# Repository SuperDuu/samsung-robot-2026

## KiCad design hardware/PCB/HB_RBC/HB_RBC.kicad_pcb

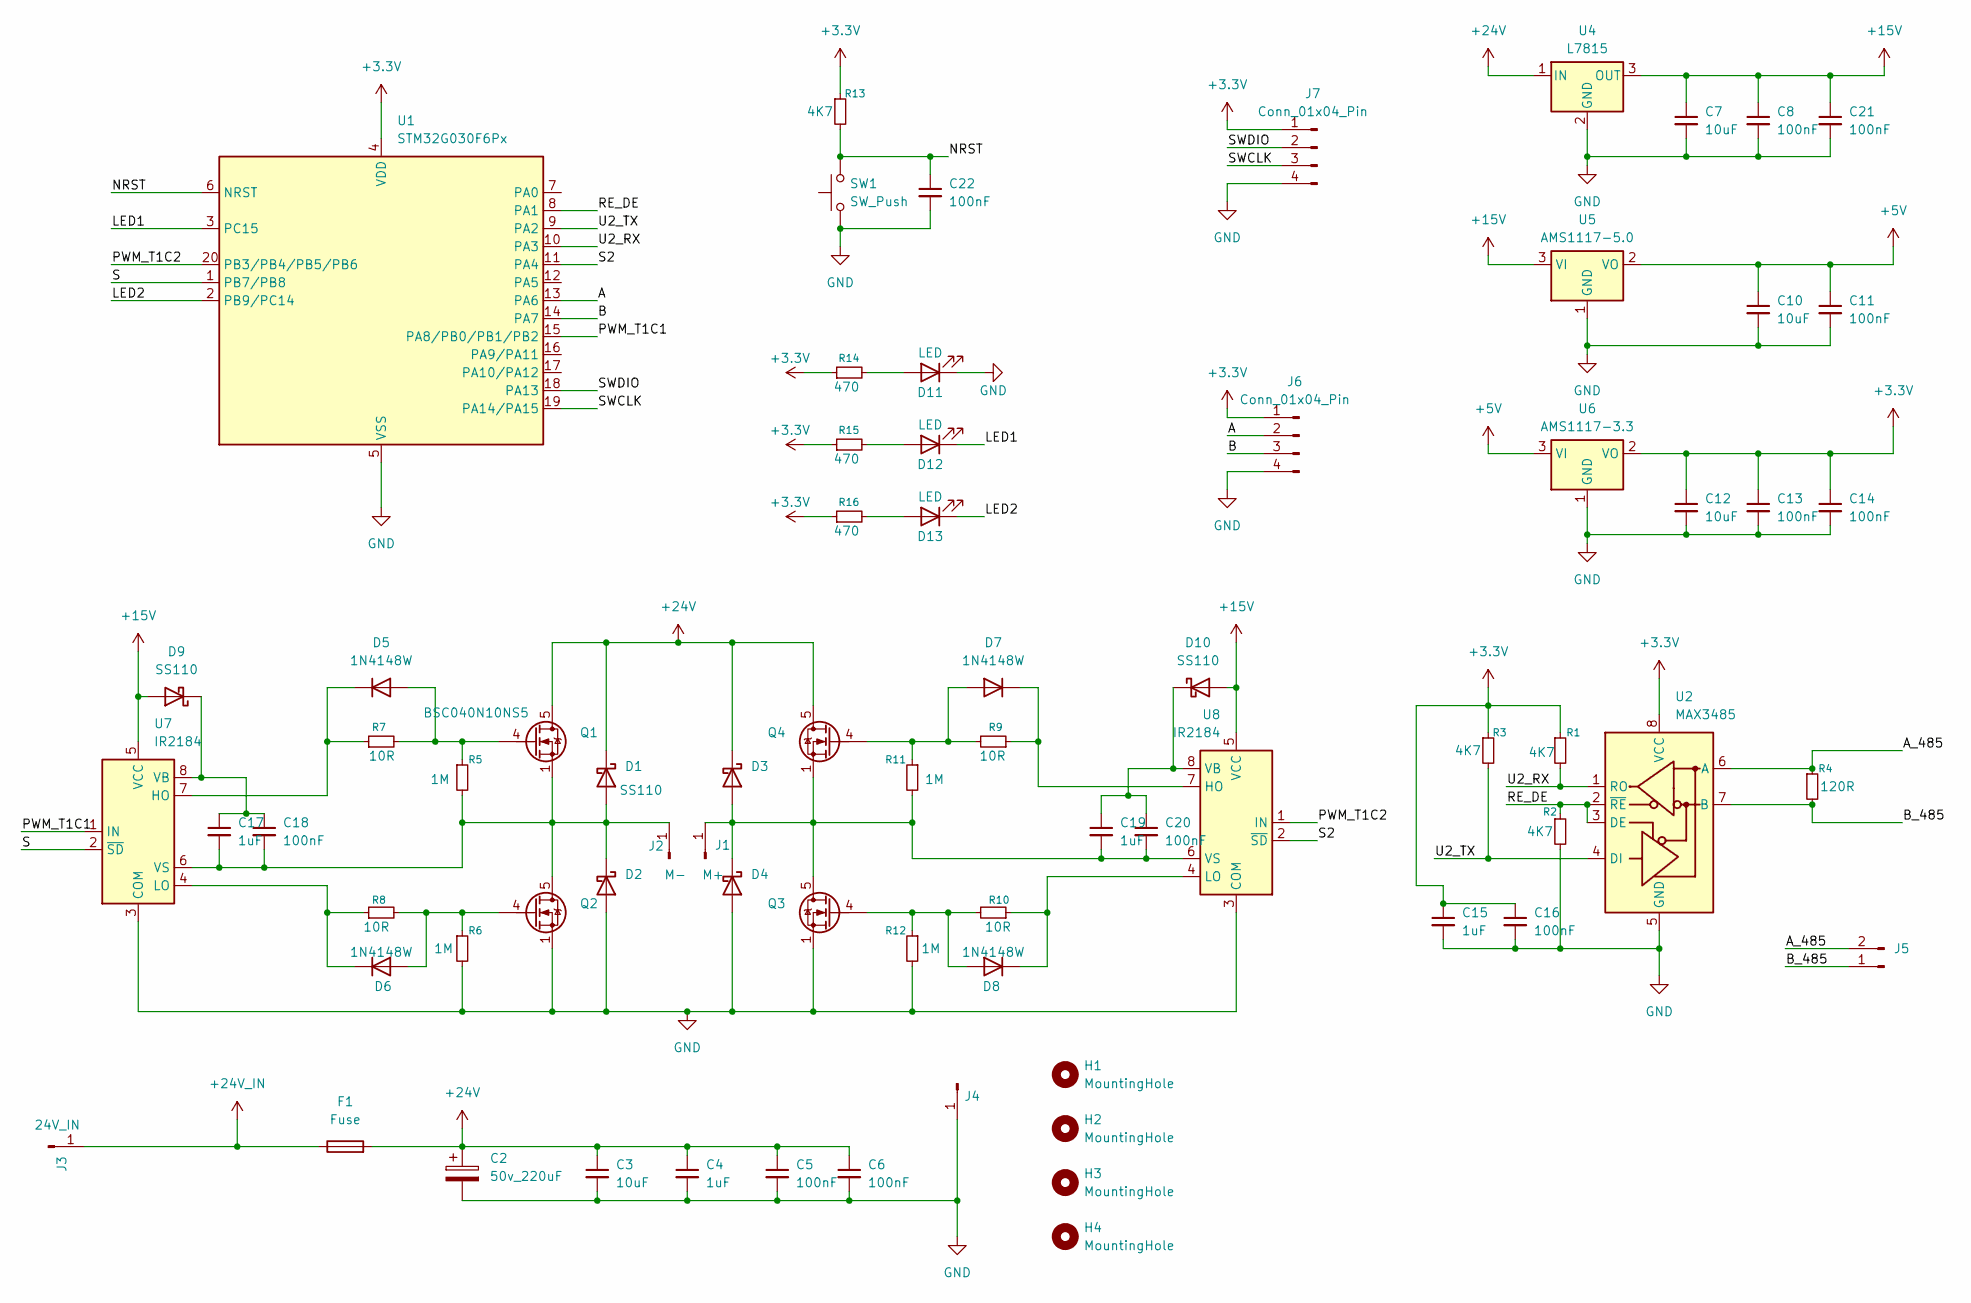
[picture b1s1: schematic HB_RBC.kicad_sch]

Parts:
C2: 50v_220uF; CP_Elec_10x10.5
C3, C7, C10, C12: 10uF; C_0805_2012Metric_Pad1.18x1.45mm_HandSolder
C4, C15, C17, C19: 1uF; C_0805_2012Metric_Pad1.18x1.45mm_HandSolder
C5, C6, C8, C11, C13, C14, C16, C18, C20, C21, C22: 100nF; C_0805_2012Metric_Pad1.18x1.45mm_HandSolder
D1, D9, D10: SS110; D_SMA
D2, D3, D4: D_Schottky; D_SMA
D5, D6, D7, D8: 1N4148W; D_SOD-123
D11, D12, D13: LED; LED_0805_2012Metric_Pad1.15x1.40mm_HandSolder
F1: Fuse; Fuseholder_Cylinder-5x20mm_Schurter_0031_8201_Horizontal_Op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
H1, H2, H3, H4: MountingHole; MountingHole_3.2mm_M3_ISO14580_Pad_TopBottom
J1: M+; SolderWirePad_1x01_SMD_4x8mm
J2: M-; SolderWirePad_1x01_SMD_4x8mm
J3: 24V_IN; SolderWirePad_1x01_SMD_4x8mm
J4: Conn_01x01_Pin; SolderWirePad_1x01_SMD_4x8mm
J5: Conn_01x02_Pin; JST_XH_S2B-XH-A-1_1x02_P2.50mm_Horizontal
J6, J7: Conn_01x04_Pin; JST_XH_S4B-XH-A-1_1x04_P2.50mm_Horizontal
Q1, Q2, Q3, Q4: BSC040N10NS5; TDSON-8-1
R1, R2, R3, R13: 4K7; R_0805_2012Metric_Pad1.20x1.40mm_HandSolder
R4: 120R; R_0805_2012Metric_Pad1.20x1.40mm_HandSolder
R5, R6, R11, R12: 1M; R_0805_2012Metric_Pad1.20x1.40mm_HandSolder
R7, R8, R9, R10: 10R; R_0805_2012Metric_Pad1.20x1.40mm_HandSolder
R14, R15, R16: 470; R_0805_2012Metric_Pad1.20x1.40mm_HandSolder
SW1: SW_Push; SW_Tactile_SPST_NO_Straight_CK_PTS636Sx25SMTRLFS
U1: STM32G030F6Px; TSSOP-20_4.4x6.5mm_P0.65mm
U2: MAX3485; SOIC-8_3.9x4.9mm_P1.27mm
U4: L7815; TO-263-3_TabPin2
U5: AMS1117-5.0; SOT-223-3_TabPin2
U6: AMS1117-3.3; SOT-223-3_TabPin2
U7, U8: IR2184; SOIC-8_3.9x4.9mm_P1.27mm

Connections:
+3.3V: C12.1, C13.1, C14.1, C15.1, C16.1, J6.1, J7.1, R1.1, R3.1, R13.1, R14.1, R15.1, R16.1, U1.4 (VDD), U2.8 (VCC), U6.2 (VO)
+5V: C10.1, C11.1, U5.2 (VO), U6.3 (VI)
+15V: C7.1, C8.1, C21.1, D9.2 (A), D10.2 (A), U4.3 (OUT), U5.3 (VI), U7.5 (VCC), U8.5 (VCC)
+24V: C2.1, C3.1, C4.1, C5.1, C6.1, D1.1 (K), D3.1 (K), F1.2, Q1.5 (D), Q4.5 (D), U4.1 (IN)
+24V_IN: F1.1, J3.1 (Pin_1_1)
/A: J6.2, U1.13 (PA6)
/A_485: J5.2, R4.1, U2.6 (A)
/B: J6.3, U1.14 (PA7)
/B_485: J5.1, R4.2, U2.7 (B)
/LED1: D12.1 (K), U1.3 (PC15)
/LED2: D13.1 (K), U1.2 (PB9/PC14)
/NRST: C22.1, R13.2, SW1.2, U1.6 (NRST)
/PWM_T1C1: U1.15 (PA8/PB0/PB1/PB2), U7.1 (IN)
/PWM_T1C2: U1.20 (PB3/PB4/PB5/PB6), U8.1 (IN)
/RE_DE: R2.1, U1.8 (PA1), U2.2 (~RE), U2.3 (DE)
/S: U1.1 (PB7/PB8), U7.2 (~SD)
/S2: U1.11 (PA4), U8.2 (~SD)
/SWCLK: J7.3, U1.19 (PA14/PA15)
/SWDIO: J7.2, U1.18 (PA13)
/U2_RX: R1.2, U1.10 (PA3), U2.1 (RO)
/U2_TX: R3.2, U1.9 (PA2), U2.4 (DI)
GND: C2.2, C3.2, C4.2, C5.2, C6.2, C7.2, C8.2, C10.2, C11.2, C12.2, C13.2, C14.2, C15.2, C16.2, C21.2, C22.2, D2.2 (A), D4.2 (A), D11.1 (K), J4.1 (Pin_1_1), J6.4, J7.4, Q2.1 (S), Q2.2 (S), Q2.3 (S), Q3.1 (S), Q3.2 (S), Q3.3 (S), R2.2, R6.2, R12.2, SW1.1, U1.5 (VSS), U2.5 (GND), U4.2 (GND), U5.1 (GND), U6.1 (GND), U7.3 (COM), U8.3 (COM)
unnamed: C17.2, C18.2, D1.2 (A), D2.1 (K), J2.1 (Pin_1_1), Q1.1 (S), Q1.2 (S), Q1.3 (S), Q2.5 (D), R5.2, U7.6 (VS)
unnamed: C19.2, C20.2, D3.2 (A), D4.1 (K), J1.1 (Pin_1_1), Q3.5 (D), Q4.1 (S), Q4.2 (S), Q4.3 (S), R11.2, U8.6 (VS)
unnamed: D5.2 (A), Q1.4 (G), R5.1, R7.2
unnamed: D5.1 (K), R7.1, U7.7 (HO)
unnamed: D6.2 (A), Q2.4 (G), R6.1, R8.2
unnamed: D6.1 (K), R8.1, U7.4 (LO)
unnamed: D7.2 (A), Q4.4 (G), R9.2, R11.1
unnamed: D7.1 (K), R9.1, U8.7 (HO)
unnamed: D8.2 (A), Q3.4 (G), R10.2, R12.1
unnamed: D8.1 (K), R10.1, U8.4 (LO)
unnamed: C17.1, C18.1, D9.1 (K), U7.8 (VB)
unnamed: C19.1, C20.1, D10.1 (K), U8.8 (VB)
unnamed: D11.2 (A), R14.2
unnamed: D12.2 (A), R15.2
unnamed: D13.2 (A), R16.2

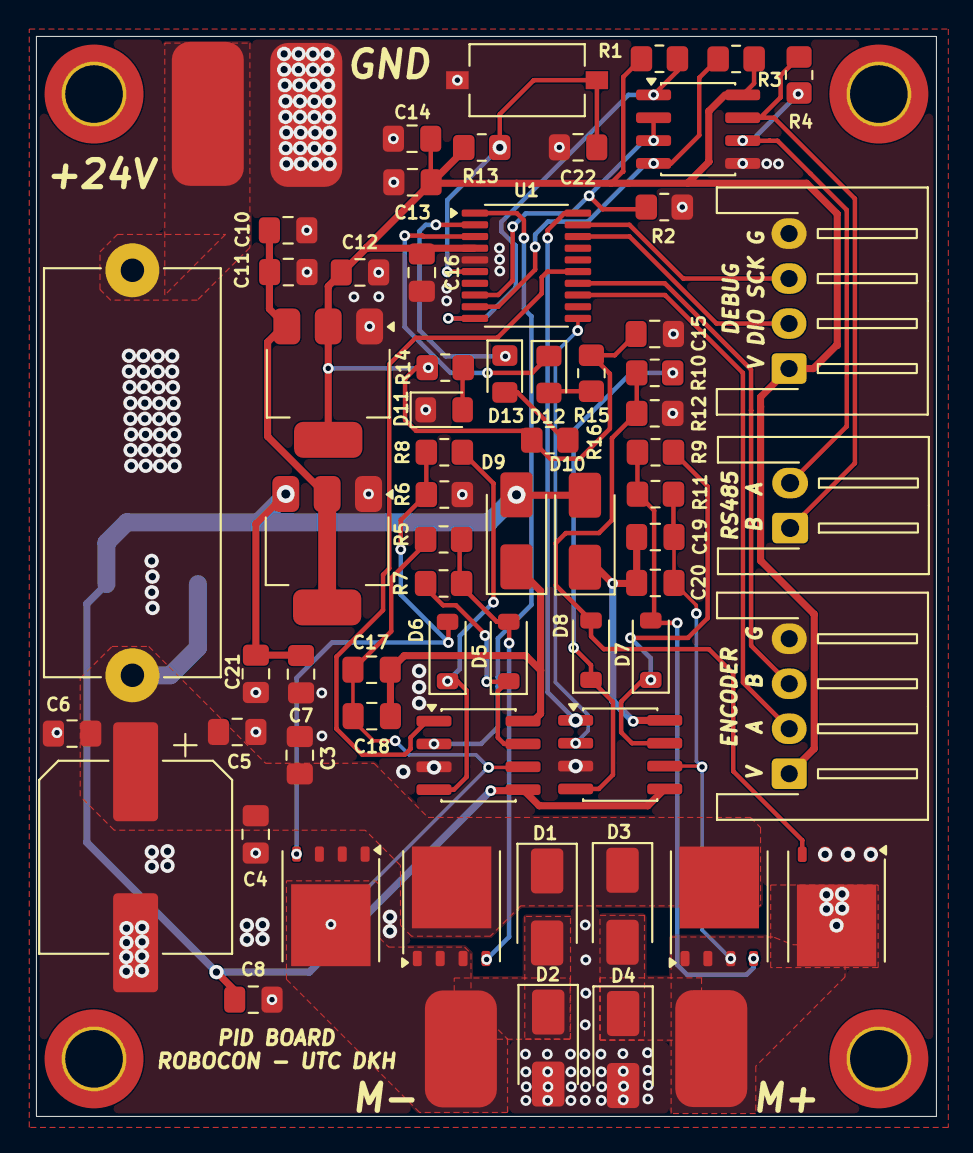
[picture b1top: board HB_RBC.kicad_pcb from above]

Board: 2 copper layers, 50.0 x 60.0 mm, 73 parts (1 on the bottom side), 37 nets.

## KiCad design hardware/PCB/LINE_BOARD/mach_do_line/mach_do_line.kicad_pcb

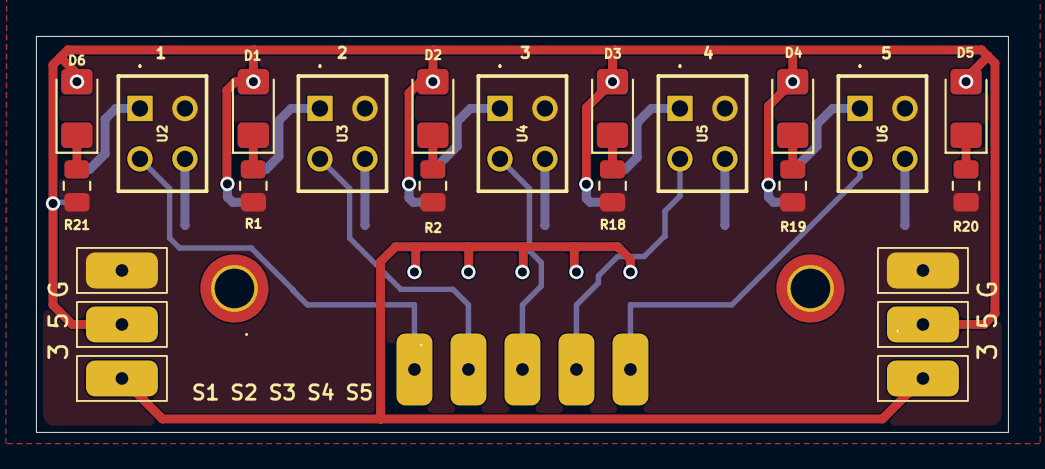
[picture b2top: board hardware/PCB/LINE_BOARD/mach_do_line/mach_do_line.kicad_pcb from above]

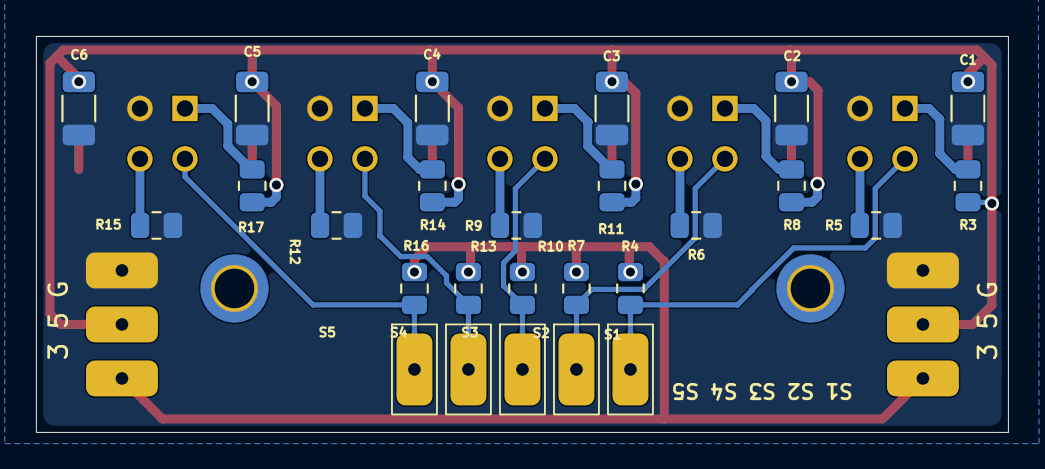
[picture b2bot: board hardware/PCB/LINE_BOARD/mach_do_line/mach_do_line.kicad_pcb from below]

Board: 2 copper layers, 54.0 x 22.0 mm, 51 parts (26 on the bottom side), 24 nets.

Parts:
C1, C2, C3, C4, C5, C6: 100uF; C_1206_3216Metric
D1, D2, D3, D4, D5, D6: LED_Small; LED_1206_3216Metric_Pad1.42x1.75mm_HandSolder
H1, H2: MountingHole; MountingHole_2.2mm_M2_ISO14580_Pad_TopBottom
J2, J3, J10, J11, J12, J13, J14, J15, J16, J17, J18: Conn_01x01_Pin; PAD-2x4mm-SMD
R1, R2, R18, R19, R20, R21: 220; R_0805_2012Metric
R3, R8, R11, R14, R17: 220R; R_0805_2012Metric
R4, R7, R10, R13, R16: 10K; R_0805_2012Metric
R5, R6, R9, R12, R15: 100R; R_0805_2012Metric
U2, U3, U4, U5, U6: RPR-220; RPR220

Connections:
+3V3: J3.1 (Pin_1_1), J15.1 (Pin_1_1), R4.2, R7.2, R10.2, R13.2, R16.2
+5V: C1.1, C2.1, C3.1, C4.1, C5.1, C6.1, D1.2 (A), D2.2 (A), D3.2 (A), D4.2 (A), D5.2 (A), D6.2 (A), J13.1 (Pin_1_1), J16.1 (Pin_1_1), R3.1, R8.1, R11.1, R14.1, R17.1
/s1: J2.1 (Pin_1_1), R4.1, U2.4 (C)
/s2: J10.1 (Pin_1_1), R7.1, U3.4 (C)
/s3: J11.1 (Pin_1_1), R10.1, U4.4 (C)
/s4: J12.1 (Pin_1_1), R13.1, U5.4 (C)
/s5: J18.1 (Pin_1_1), R16.1, U6.4 (C)
GND: C1.2, C2.2, C3.2, C4.2, C5.2, C6.2, J14.1 (Pin_1_1), J17.1 (Pin_1_1), R1.2, R2.2, R5.2, R6.2, R9.2, R12.2, R15.2, R18.2, R19.2, R20.2, R21.2, U2.2 (K), U3.2 (K), U4.2 (K), U5.2 (K), U6.2 (K)
unnamed: D1.1 (K), R1.1
unnamed: D2.1 (K), R2.1
unnamed: D3.1 (K), R18.1
unnamed: D4.1 (K), R19.1
unnamed: D5.1 (K), R20.1
unnamed: D6.1 (K), R21.1
unnamed: R3.2, U2.1 (A)
unnamed: R5.1, U2.3 (E)
unnamed: R8.2, U3.1 (A)
unnamed: R6.1, U3.3 (E)
unnamed: R11.2, U4.1 (A)
unnamed: R9.1, U4.3 (E)
unnamed: R14.2, U5.1 (A)
unnamed: R12.1, U5.3 (E)
unnamed: R17.2, U6.1 (A)
unnamed: R15.1, U6.3 (E)

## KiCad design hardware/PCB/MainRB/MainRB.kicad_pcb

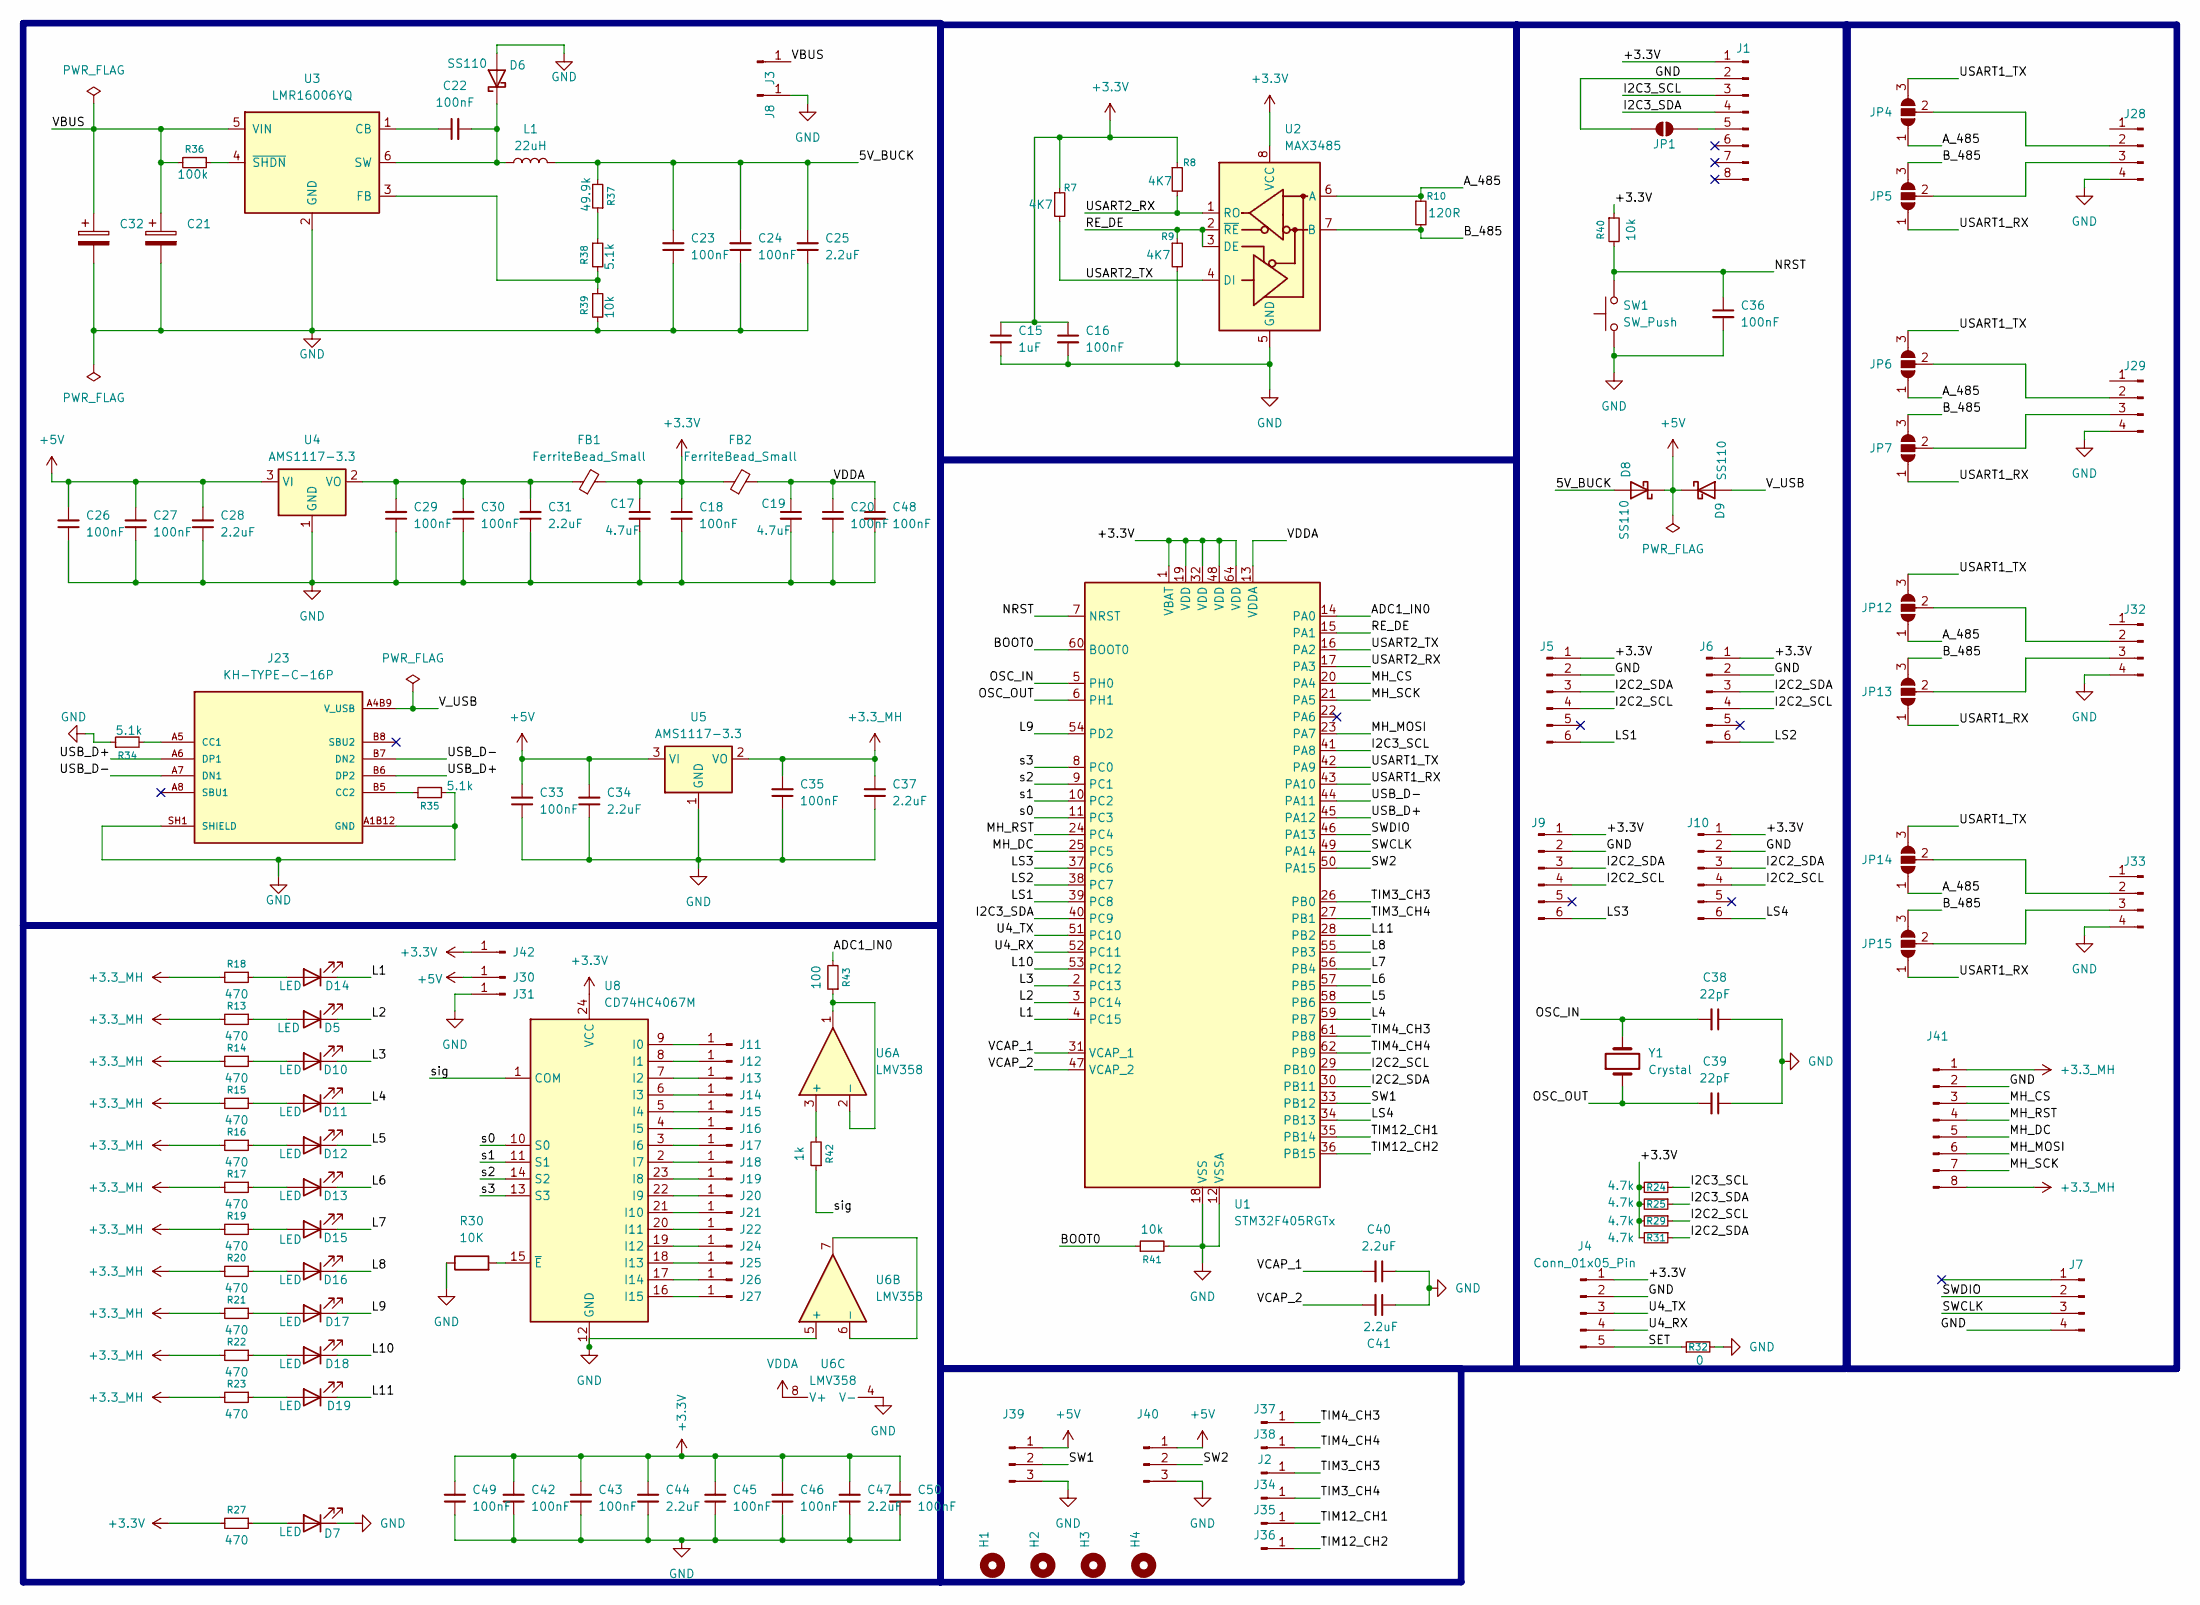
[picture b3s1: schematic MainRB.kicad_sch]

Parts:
C15: 1uF; C_0805_2012Metric_Pad1.18x1.45mm_HandSolder
C16, C18, C20, C22, C23, C24, C26, C27, C29, C30, C33, C35, C36, C42, C43, C45, C46, C48, C49, C50: 100nF; C_0805_2012Metric_Pad1.18x1.45mm_HandSolder
C17, C19: 4.7uF; C_0805_2012Metric_Pad1.18x1.45mm_HandSolder
C21, C32: C_Polarized; CP_Elec_10x10.5
C25, C28, C31, C34, C37, C40, C41, C44, C47: 2.2uF; C_0805_2012Metric_Pad1.18x1.45mm_HandSolder
C38, C39: 22pF; C_0805_2012Metric_Pad1.18x1.45mm_HandSolder
D5, D7, D10, D11, D12, D13, D14, D15, D16, D17, D18, D19: LED; LED_0805_2012Metric
D6, D8, D9: SS110; D_SMA
FB1, FB2: FerriteBead_Small; L_0603_1608Metric_Pad1.05x0.95mm_HandSolder
H1, H2, H3, H4: MountingHole; MountingHole_3.2mm_M3_ISO14580_Pad_TopBottom
J1: Conn_01x08_Pin; PinHeader_1x08_P2.54mm_Vertical
J2, J34, J35, J36, J37, J38: Conn_01x01_Pin; SolderWirePad_1x01_SMD_2x4mm
J3, J8: 24V_IN; SolderWirePad_1x01_SMD_4x8mm
J4: Conn_01x05_Pin; PinHeader_1x05_P2.54mm_Vertical
J5, J6, J9, J10: Conn_01x06_Pin; JST_XH_S6B-XH-A_1x06_P2.50mm_Horizontal
J7: Conn_01x04_Pin; JST_XH_B4B-XH-A_1x04_P2.50mm_Vertical
J11, J12, J13, J14, J15, J16, J17, J18, J19, J20, J21, J22, J24, J25, J26, J27, J30, J31, J42: Conn_01x01_Pin; SolderWirePad_1x01_SMD_1x2mm
J23: KH-TYPE-C-16P; KINGHELM_KH-TYPE-C-16P; PARTREV A0
J28, J29, J32, J33: Conn_01x04_Pin; JST_XH_S4B-XH-A-1_1x04_P2.50mm_Horizontal
J39, J40: Conn_01x03_Pin; JST_XH_B3B-XH-A_1x03_P2.50mm_Vertical
J41: Conn_01x08_Pin; JST_XH_B8B-XH-A_1x08_P2.50mm_Vertical
JP1: SolderJumper_2_Open; SolderJumper-2_P1.3mm_Open_Pad1.0x1.5mm
JP4, JP5, JP6, JP7, JP12, JP13, JP14, JP15: SolderJumper_3_Open; SolderJumper-3_P1.3mm_Open_RoundedPad1.0x1.5mm_NumberLabels
L1: 22uH; L_TracoPower_TCK-047_5.2x5.8mm
R7, R8, R9: 4K7; R_0805_2012Metric_Pad1.20x1.40mm_HandSolder
R10: 120R; R_0805_2012Metric_Pad1.20x1.40mm_HandSolder
R13, R14, R15, R16, R17, R18, R19, R20, R21, R22, R23, R27: 470; R_0805_2012Metric
R24, R25, R29, R31: 4.7k; R_0805_2012Metric
R30: 10K; R_0805_2012Metric
R32: 0; R_0805_2012Metric
R34, R35, R38: 5.1k; R_0805_2012Metric
R36: 100k; R_0805_2012Metric
R37: 49.9k; R_0805_2012Metric
R39, R40, R41: 10k; R_0805_2012Metric
R42: 1k; R_0805_2012Metric
R43: 100; R_0805_2012Metric
SW1: SW_Push; SW_Tactile_SPST_NO_Straight_CK_PTS636Sx25SMTRLFS
U1: STM32F405RGTx; LQFP-64_10x10mm_P0.5mm
U2: MAX3485; SOIC-8_3.9x4.9mm_P1.27mm
U3: LMR16006YQ; SOT-23-6
U4, U5: AMS1117-3.3; SOT-223-3_TabPin2
U6: LMV358; SOIC-8_3.9x4.9mm_P1.27mm
U8: CD74HC4067M; SOIC-24W_7.5x15.4mm_P1.27mm
Y1: Crystal; Crystal_HC49-4H_Vertical

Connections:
+3.3V: C15.1, C16.1, C17.1, C18.1, C42.2, C43.2, C44.2, C45.2, C46.2, C47.2, C49.2, C50.2, FB1.2, FB2.1, J1.1, J4.1, J5.1, J6.1, J9.1, J10.1, J42.1 (Pin_1_1), R7.1, R8.1, R24.2, R25.2, R27.2, R29.2, R31.2, R40.1, U1.1 (VBAT), U1.19 (VDD), U1.32 (VDD), U1.48 (VDD), U1.64 (VDD), U2.8 (VCC), U8.24 (VCC)
+3.3_MH: C35.2, C37.2, J41.1, J41.8, R13.2, R14.2, R15.2, R16.2, R17.2, R18.2, R19.2, R20.2, R21.2, R22.2, R23.2, U5.2 (VO)
+5V: C26.2, C27.2, C28.2, C33.2, C34.2, D8.1 (K), D9.1 (K), J30.1 (Pin_1_1), J39.1, J40.1, U4.3 (VI), U5.3 (VI)
/5V_BUCK: C23.2, C24.2, C25.2, D8.2 (A), L1.2, R37.2
/ADC1_IN0: R43.2, U1.14 (PA0)
/A_485: JP4.1 (A), JP6.1 (A), JP12.1 (A), JP14.1 (A), R10.1, U2.6 (A)
/BOOT0: R41.1, U1.60 (BOOT0)
/B_485: JP5.3 (B), JP7.3 (B), JP13.3 (B), JP15.3 (B), R10.2, U2.7 (B)
/I2C2_SCL: J5.4, J6.4, J9.4, J10.4, R29.1, U1.29 (PB10)
/I2C2_SDA: J5.3, J6.3, J9.3, J10.3, R31.1, U1.30 (PB11)
/I2C3_SCL: J1.3, R24.1, U1.41 (PA8)
/I2C3_SDA: J1.4, R25.1, U1.40 (PC9)
/L1: D14.1 (K), U1.4 (PC15)
/L2: D5.1 (K), U1.3 (PC14)
/L3: D10.1 (K), U1.2 (PC13)
/L4: D11.1 (K), U1.59 (PB7)
/L5: D12.1 (K), U1.58 (PB6)
/L6: D13.1 (K), U1.57 (PB5)
/L7: D15.1 (K), U1.56 (PB4)
/L8: D16.1 (K), U1.55 (PB3)
/L9: D17.1 (K), U1.54 (PD2)
/L10: D18.1 (K), U1.53 (PC12)
/L11: D19.1 (K), U1.28 (PB2)
/LS1: J5.6, U1.39 (PC8)
/LS2: J6.6, U1.38 (PC7)
/LS3: J9.6, U1.37 (PC6)
/LS4: J10.6, U1.34 (PB13)
/MH_CS: J41.3, U1.20 (PA4)
/MH_DC: J41.5, U1.25 (PC5)
/MH_MOSI: J41.6, U1.23 (PA7)
/MH_RST: J41.4, U1.24 (PC4)
/MH_SCK: J41.7, U1.21 (PA5)
/NRST: C36.1, R40.2, SW1.2, U1.7 (NRST)
/OSC_IN: C38.2, U1.5 (PH0), Y1.2
/OSC_OUT: C39.2, U1.6 (PH1), Y1.1
/RE_DE: R9.1, U1.15 (PA1), U2.2 (~RE), U2.3 (DE)
/SET: J4.5, R32.1
/SW1: J39.2, U1.33 (PB12)
/SW2: J40.2, U1.50 (PA15)
/SWCLK: J7.3, U1.49 (PA14)
/SWDIO: J7.2, U1.46 (PA13)
/TIM3_CH3: J2.1 (Pin_1_1), U1.26 (PB0)
/TIM3_CH4: J34.1 (Pin_1_1), U1.27 (PB1)
/TIM4_CH3: J37.1 (Pin_1_1), U1.61 (PB8)
/TIM4_CH4: J38.1 (Pin_1_1), U1.62 (PB9)
/TIM12_CH1: J35.1 (Pin_1_1), U1.35 (PB14)
/TIM12_CH2: J36.1 (Pin_1_1), U1.36 (PB15)
/U4_RX: J4.4, U1.52 (PC11)
/U4_TX: J4.3, U1.51 (PC10)
/USART1_RX: JP5.1 (A), JP7.1 (A), JP13.1 (A), JP15.1 (A), U1.43 (PA10)
/USART1_TX: JP4.3 (B), JP6.3 (B), JP12.3 (B), JP14.3 (B), U1.42 (PA9)
/USART2_RX: R8.2, U1.17 (PA3), U2.1 (RO)
/USART2_TX: R7.2, U1.16 (PA2), U2.4 (DI)
/USB_D+: J23.A6 (DP1), J23.B6 (DP2), U1.45 (PA12)
/USB_D-: J23.A7 (DN1), J23.B7 (DN2), U1.44 (PA11)
/VBUS: C21.1, C32.1, J3.1 (Pin_1_1), R36.2, U3.5 (VIN)
/VCAP_1: C40.2, U1.31 (VCAP_1)
/VCAP_2: C41.2, U1.47 (VCAP_2)
/s0: U1.11 (PC3), U8.10 (S0)
/s1: U1.10 (PC2), U8.11 (S1)
/s2: U1.9 (PC1), U8.14 (S2)
/s3: U1.8 (PC0), U8.13 (S3)
/sig: R42.1, U8.1 (COM)
GND: C15.2, C16.2, C17.2, C18.2, C19.2, C20.2, C21.2, C23.1, C24.1, C25.1, C26.1, C27.1, C28.1, C29.1, C30.1, C31.1, C32.2, C33.1, C34.1, C35.1, C36.2, C37.1, C38.1, C39.1, C40.1, C41.1, C42.1, C43.1, C44.1, C45.1, C46.1, C47.1, C48.2, C49.1, C50.1, D6.2 (A), D7.1 (K), J1.2, J4.2, J5.2, J6.2, J7.4, J8.1 (Pin_1_1), J9.2, J10.2, J23.A1B12 (GND), J23.A12B1 (GND), J23.SH1 (SHIELD), J23.SH2 (SHIELD), J23.SH3 (SHIELD), J23.SH4 (SHIELD), J28.4, J29.4, J31.1 (Pin_1_1), J32.4, J33.4, J39.3, J40.3, J41.2, JP1.1 (A), R9.2, R30.1, R32.2, R34.1, R35.2, R39.2, R41.2, SW1.1, U1.12 (VSSA), U1.18 (VSS), U1.63 (VSS), U2.5 (GND), U3.2 (GND), U4.1 (GND), U5.1 (GND), U6.4 (V-), U6.5 (+), U8.12 (GND)
unnamed: D5.2 (A), R13.1
unnamed: C22.2, D6.1 (K), L1.1, U3.6 (SW)
unnamed: D7.2 (A), R27.1
unnamed: D10.2 (A), R14.1
unnamed: D11.2 (A), R15.1
unnamed: D12.2 (A), R16.1
unnamed: D13.2 (A), R17.1
unnamed: D14.2 (A), R18.1
unnamed: D15.2 (A), R19.1
unnamed: D16.2 (A), R20.1
unnamed: D17.2 (A), R21.1
unnamed: D18.2 (A), R22.1
unnamed: D19.2 (A), R23.1
unnamed: J1.5, JP1.2 (B)
unnamed: J11.1 (Pin_1_1), U8.9 (I0)
unnamed: J12.1 (Pin_1_1), U8.8 (I1)
unnamed: J13.1 (Pin_1_1), U8.7 (I2)
unnamed: J14.1 (Pin_1_1), U8.6 (I3)
unnamed: J15.1 (Pin_1_1), U8.5 (I4)
unnamed: J16.1 (Pin_1_1), U8.4 (I5)
unnamed: J17.1 (Pin_1_1), U8.3 (I6)
unnamed: J18.1 (Pin_1_1), U8.2 (I7)
unnamed: J19.1 (Pin_1_1), U8.23 (I8)
unnamed: J20.1 (Pin_1_1), U8.22 (I9)
unnamed: J21.1 (Pin_1_1), U8.21 (I10)
unnamed: J22.1 (Pin_1_1), U8.20 (I11)
unnamed: J23.A5 (CC1), R34.2
unnamed: J23.B5 (CC2), R35.1
unnamed: J24.1 (Pin_1_1), U8.19 (I12)
unnamed: J25.1 (Pin_1_1), U8.18 (I13)
unnamed: J26.1 (Pin_1_1), U8.17 (I14)
unnamed: J27.1 (Pin_1_1), U8.16 (I15)
unnamed: J28.2, JP4.2 (C)
unnamed: J28.3, JP5.2 (C)
unnamed: J29.2, JP6.2 (C)
unnamed: J29.3, JP7.2 (C)
unnamed: J32.2, JP12.2 (C)
unnamed: J32.3, JP13.2 (C)
unnamed: J33.2, JP14.2 (C)
unnamed: J33.3, JP15.2 (C)
unnamed: R37.1, R38.1
unnamed: C22.1, U3.1 (CB)
unnamed: R38.2, R39.1, U3.3 (FB)
unnamed: R36.1, U3.4 (~SHDN)
unnamed: C29.2, C30.2, C31.2, FB1.1, U4.2 (VO)
unnamed: R42.2, U6.3 (+)
unnamed: R43.1, U6.1, U6.2 (-)
unnamed: U6.6 (-), U6.7
unnamed: R30.2, U8.15 (~E)
VDDA: C19.1, C20.1, C48.1, FB2.2, U1.13 (VDDA), U6.8 (V+)
V_USB: D9.2 (A), J23.A4B9 (V_USB), J23.A9B4 (V_USB)

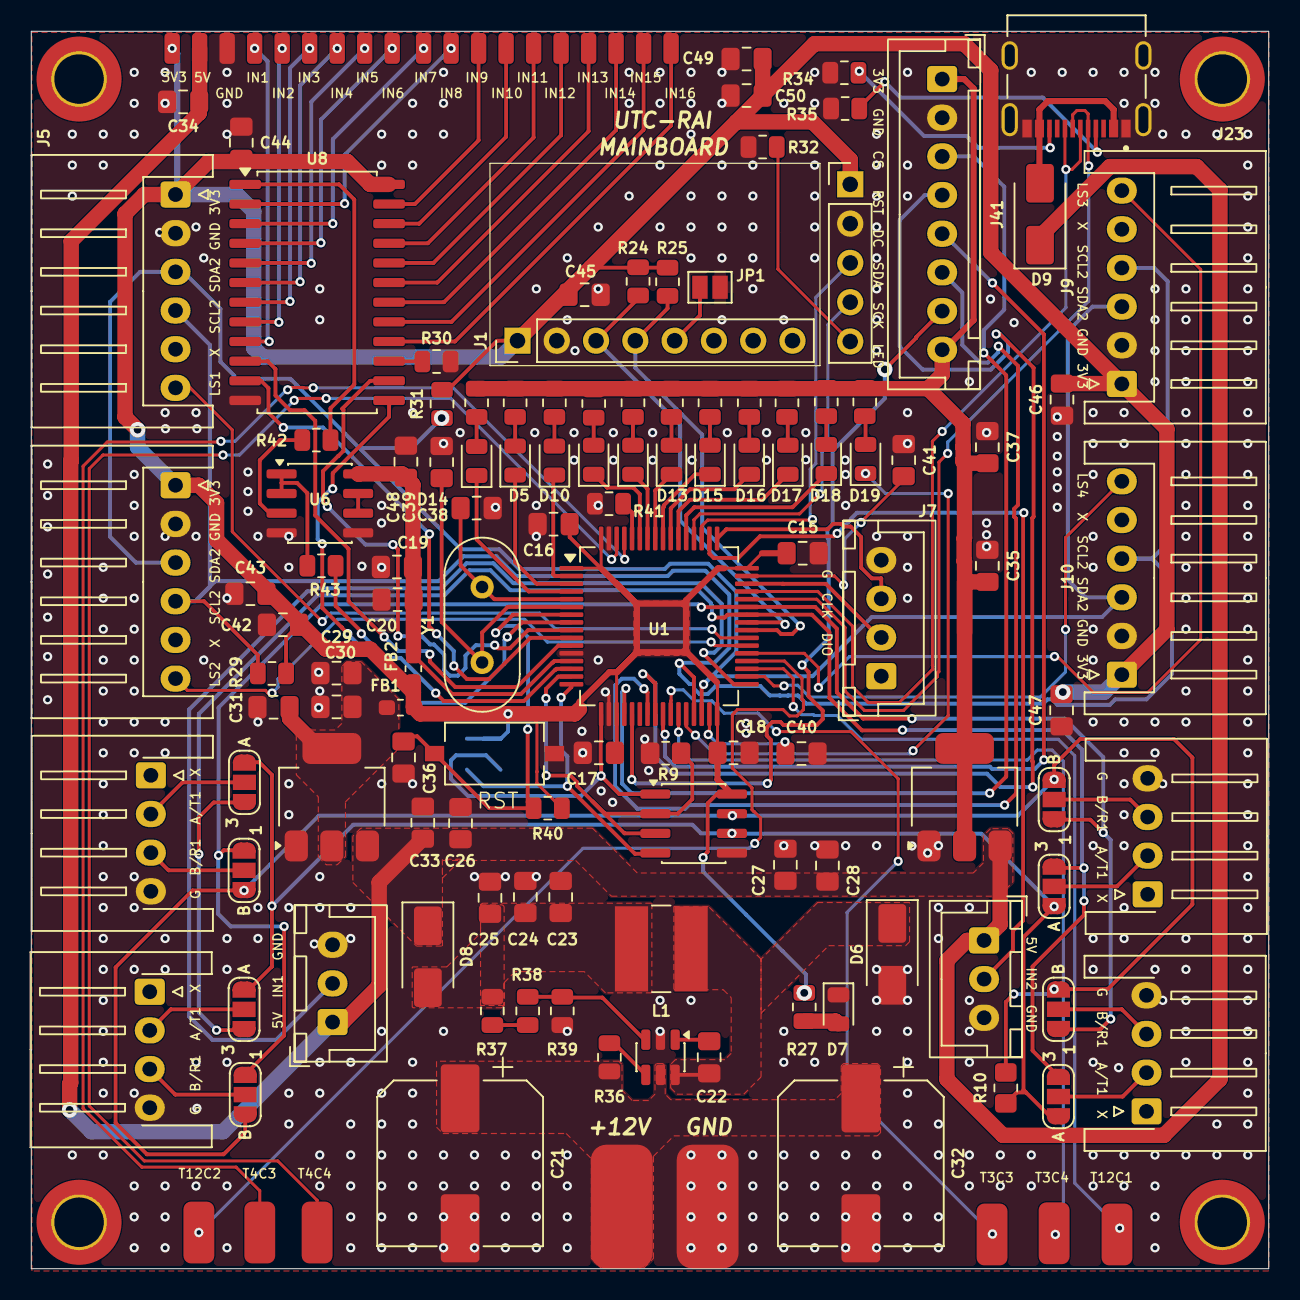
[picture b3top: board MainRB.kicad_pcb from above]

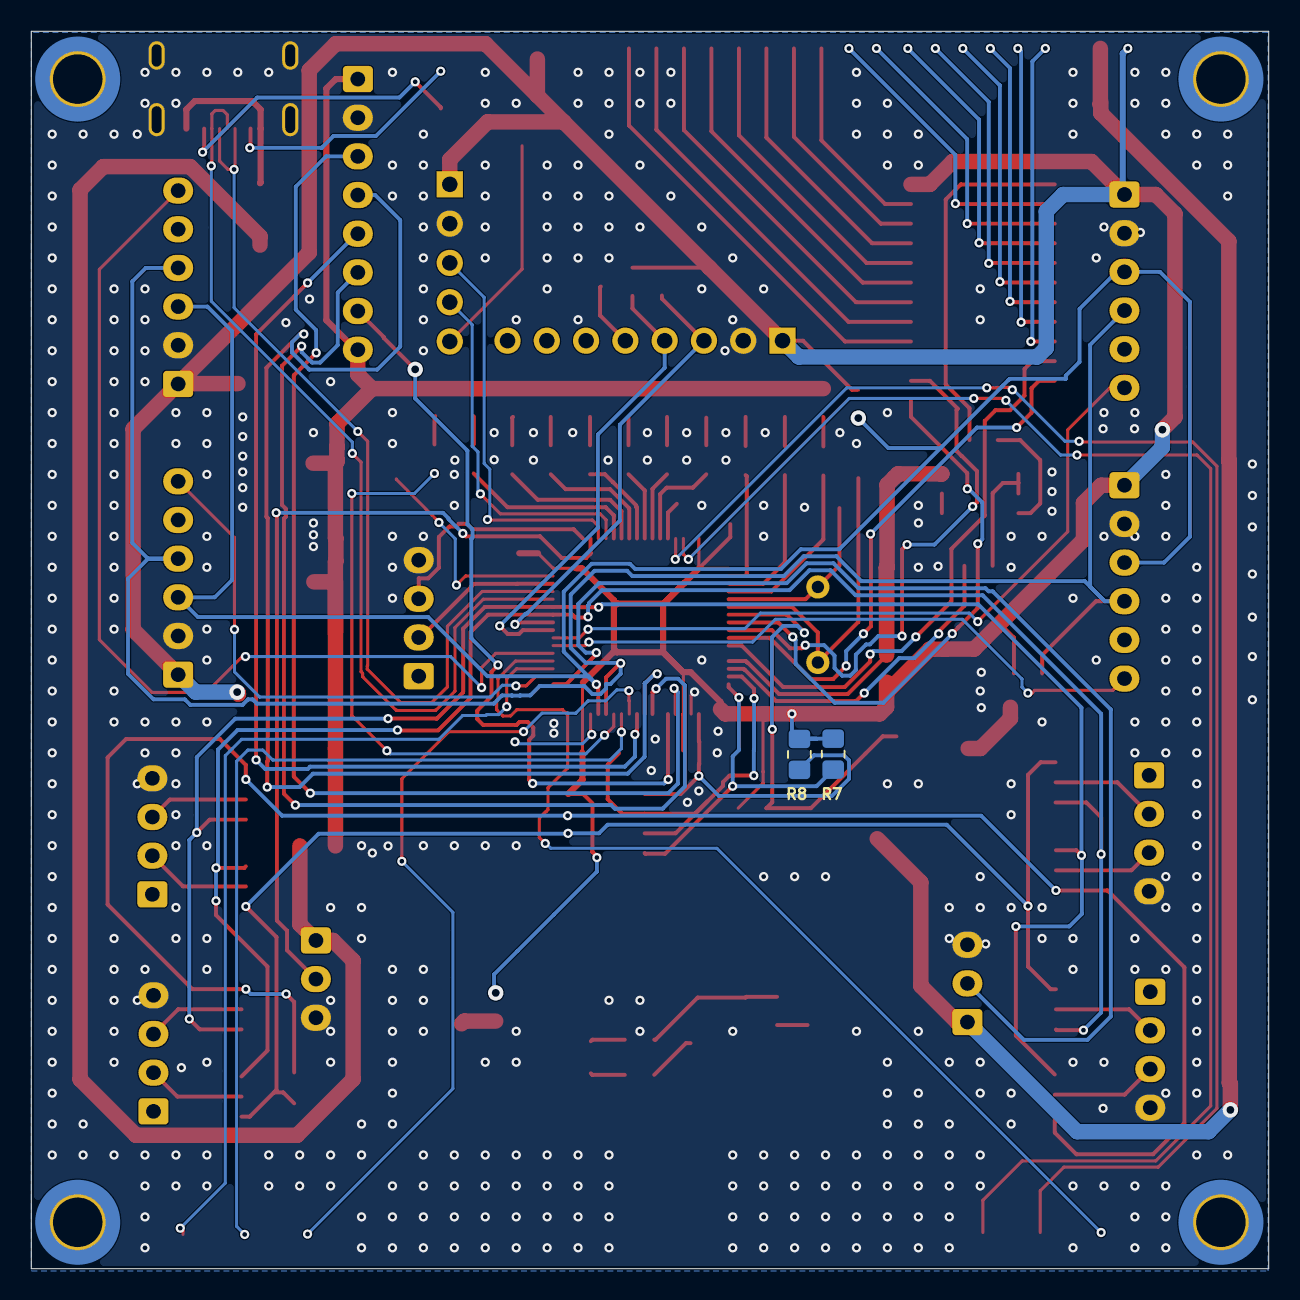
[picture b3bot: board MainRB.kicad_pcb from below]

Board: 2 copper layers, 80.0 x 80.0 mm, 150 parts (2 on the bottom side), 115 nets.

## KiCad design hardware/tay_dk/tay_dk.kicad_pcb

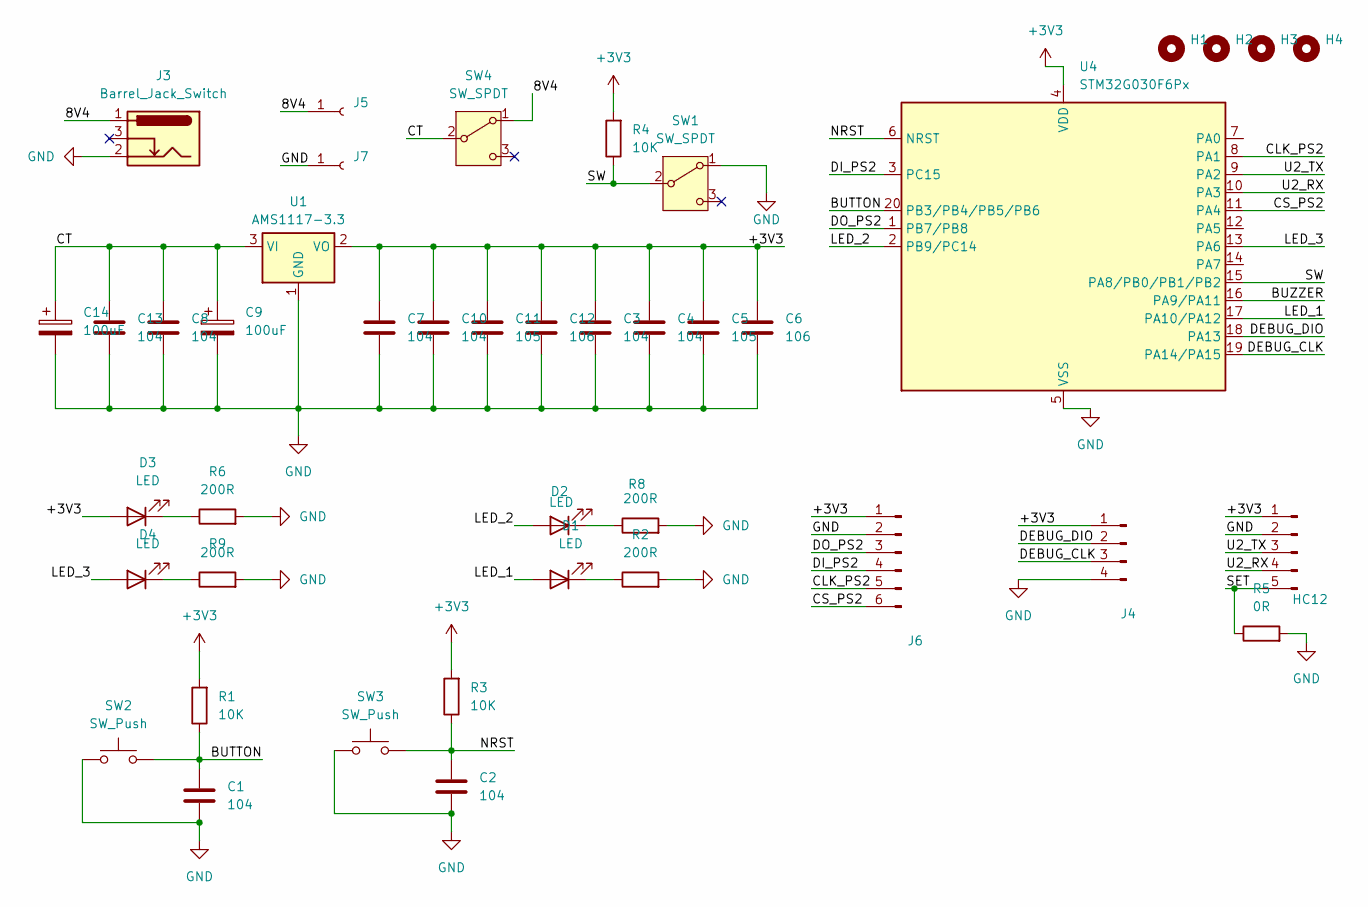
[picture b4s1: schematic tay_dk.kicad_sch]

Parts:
C1, C2, C3, C4, C7, C8, C10, C13: 104; C_0805_2012Metric
C5, C11: 105; C_0805_2012Metric
C6, C12: 106; C_0805_2012Metric
C9, C14: 100uF; CP_Elec_6.3x5.4_Nichicon
D1, D2, D3, D4: LED; LED_0805_2012Metric
H1, H2, H3, H4: MountingHole; MountingHole_3.2mm_M3_ISO14580_Pad_TopBottom
J2: HC12; PinHeader_1x05_P2.54mm_Vertical
J3: Barrel_Jack_Switch; BarrelJack_GCT_DCJ200-10-A_Horizontal
J4: Conn_01x04_Pin; JST_XH_S4B-XH-A-1_1x04_P2.50mm_Horizontal
J5, J7: Conn_01x01_Socket; SolderWirePad_1x01_SMD_3x6mm
J6: Conn_01x06_Pin; JST_XH_S6B-XH-A-1_1x06_P2.50mm_Horizontal
R1, R3, R4: 10K; R_0805_2012Metric
R2, R6, R8, R9: 200R; R_0805_2012Metric
R5: 0R; R_0805_2012Metric
SW1, SW4: SW_SPDT; SW_Slide_SPDT_Straight_CK_OS102011MS2Q
SW2, SW3: SW_Push; SW_Tactile_SPST_NO_Straight_CK_PTS636Sx25SMTRLFS
U1: AMS1117-3.3; SOT-223-3_TabPin2
U4: STM32G030F6Px; TSSOP-20_4.4x6.5mm_P0.65mm

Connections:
+3V3: C3.1, C4.1, C5.1, C6.1, C7.1, C10.1, C11.1, C12.1, D3.2 (A), J2.1, J4.1, J6.1, R1.2, R3.2, R4.2, U1.2 (VO), U4.4 (VDD)
/8V4: J3.1, J5.1 (Pin_1_1), SW4.1 (A)
/BUTTON: C1.1, R1.1, SW2.2, U4.20 (PB3/PB4/PB5/PB6)
/BUZZER: U4.16 (PA9/PA11)
/CLK_PS2: J6.5, U4.8 (PA1)
/CS_PS2: J6.6, U4.11 (PA4)
/CT: C8.1, C9.1, C13.1, C14.1, SW4.2 (B), U1.3 (VI)
/DEBUG_CLK: J4.3, U4.19 (PA14/PA15)
/DEBUG_DIO: J4.2, U4.18 (PA13)
/DI_PS2: J6.4, U4.3 (PC15)
/DO_PS2: J6.3, U4.1 (PB7/PB8)
/LED_1: D1.2 (A), U4.17 (PA10/PA12)
/LED_2: D2.2 (A), U4.2 (PB9/PC14)
/LED_3: D4.2 (A), U4.13 (PA6)
/NRST: C2.1, R3.1, SW3.2, U4.6 (NRST)
/SET: J2.5, R5.1
/SW: R4.1, SW1.2 (B), U4.15 (PA8/PB0/PB1/PB2)
/U2_RX: J2.4, U4.10 (PA3)
/U2_TX: J2.3, U4.9 (PA2)
GND: C1.2, C2.2, C3.2, C4.2, C5.2, C6.2, C7.2, C8.2, C9.2, C10.2, C11.2, C12.2, C13.2, C14.2, J2.2, J3.2, J4.4, J6.2, J7.1 (Pin_1_1), R2.2, R5.2, R6.2, R8.2, R9.2, SW1.1 (A), SW2.1, SW3.1, U1.1 (GND), U4.5 (VSS)
unnamed: D1.1 (K), R2.1
unnamed: D2.1 (K), R8.1
unnamed: D3.1 (K), R6.1
unnamed: D4.1 (K), R9.1
